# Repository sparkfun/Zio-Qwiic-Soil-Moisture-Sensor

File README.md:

SparkFun Qwiic Soil Moisture Sensor
========================================

[*SparkFun Qwiic Soil Moisture Sensor (17731)*](https://www.sparkfun.com/products/17731)

The SparkFun Qwiic Soil Moisture Sensor is a simple breakout for measuring the moisture in soil and similar materials. The soil moisture sensor is pretty straightforward to use. The two large, exposed pads function as probes for the sensor, together acting as a variable resistor. The more water that is in the soil means the better the conductivity between the pads will be, resulting in a lower resistance and a higher SIG out. This version of the Soil Moisture Sensor includes a Qwiic connector, making it even easier to use this sensor!

To get the SparkFun Soil Moisture Sensor functioning, all you will need is to connect the VCC and GND pins to your Arduino-based device (or compatible development board). You will receive a SIG out, which will depend on the amount of water in the soil. One commonly known issue with soil moisture senors is their short lifespan when exposed to a moist environment. To combat this, we’ve had the PCB coated in gold finishing (ENIG, or Electroless Nickel Immersion Gold).

Built in cooperation with [Zio Smart Prototyping](https://www.smart-prototyping.com/Zio/Zio-Qwiic-Soil-Moisture-Sensor)! 

#### Specification

* I2C address: 0x07- 0x78 (Default: 0x28)
* Gateway MCU: ATtiny85-20SU
* Probes Surface Finish: Gold Immersion
* Weight: 6.0g
* Module dimension: 20.3x 100.0mm

Documentation
--------------
* **[Hookup Guide](https://learn.sparkfun.com/tutorials/soil-moisture-sensor-hookup-guide)** - Basic hookup guide for the SparkFun Qwiic Soil Moisture Sensor.
* [ATtiny85 Gateway Firmware](https://github.com/ZIOCC/Zio-Qwiic-Soil-Moisture-Sensor/tree/master/Firmware/Qwiic_Soil_Moisture_Sensor_Gateway_Firmware/Qwiic_Soil_Moisture_Firmware)

License Information
-------------------

This product is _**open source**_! 

Please review the LICENSE.md file for license information. 

If you have any questions or concerns on licensing, please contact technical support on our [SparkFun forums](https://forum.sparkfun.com/viewforum.php?f=152).

Distributed as-is; no warranty is given.

- Your friends at SparkFun.

_<COLLABORATION CREDIT>_

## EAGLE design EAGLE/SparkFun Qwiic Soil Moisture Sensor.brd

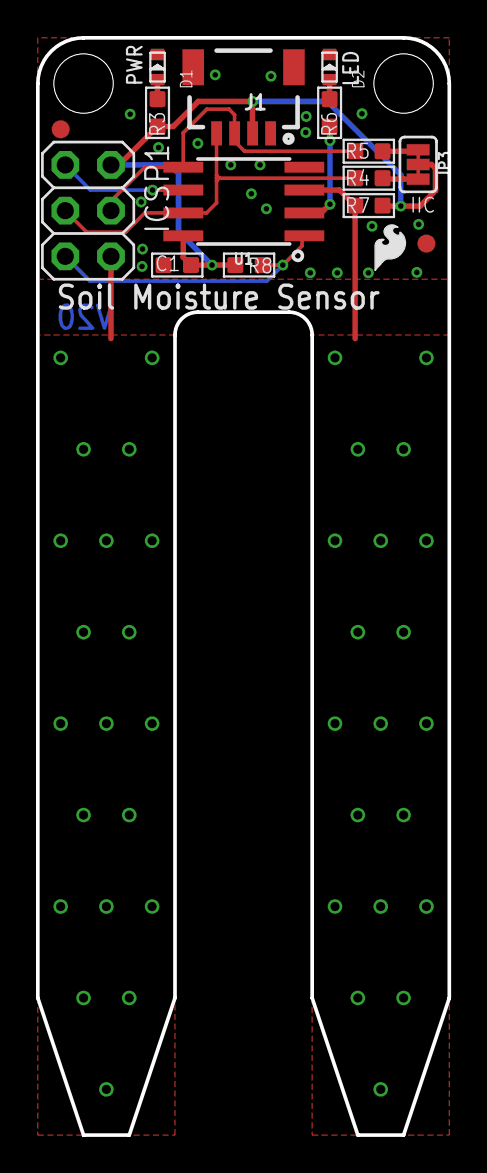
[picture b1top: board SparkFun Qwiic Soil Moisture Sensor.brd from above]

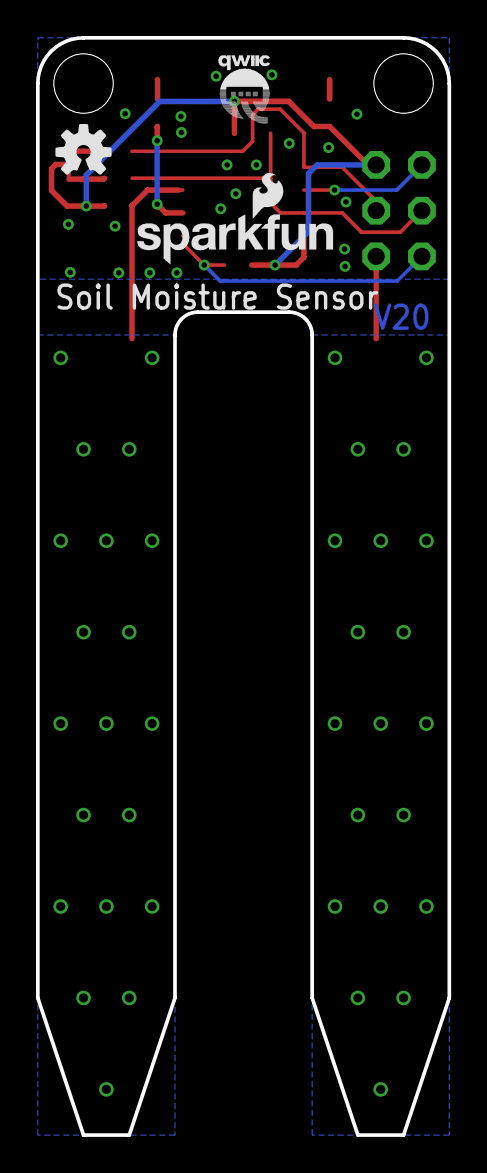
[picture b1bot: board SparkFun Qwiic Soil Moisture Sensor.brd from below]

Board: 2 copper layers, 22.9 x 61.0 mm, 21 parts (3 on the bottom side), 12 nets.

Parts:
C1: 100nF ±10% 50V; C0603
D1: RED; LED-0603
D2: GREEN; LED-0603
FID1, FID2: FIDUCIAL1X2; FIDUCIAL-1X2
ICSP1: 3x2 M; 2X03
J1: JST-SH-4P-1.0; JST-SH-4P
JP3: SMT-JUMPER_3_2-NC_TRACE
LOGO1: SFE_LOGO_NAME_FLAME.1_INCH; SFE_LOGO_NAME_FLAME_.1
LOGO2: OSHW-LOGOS; OSHW-LOGO-S
R3, R6: 1.5K ±1%; R0603
R4, R5: 4.7K ±1%; R0603
R7: 100K ±1%; R0603
R8: 10K ±1%; R0603
STANDOFF1, STANDOFF2: STAND-OFF
U1: Tiny85-20-SMT; SO08-EIAJ_MCU
U$2: SFE_LOGO_FLAME_.1
U$5: QWIIC-LOGO-SMALL

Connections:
+3V3: C1.2, ICSP1.2, J1.2, JP3.2, R3.1, R7.2, R8.2, U1.8
ADC: R7.1, U1.3
GND: C1.1, D1.-, D2.-, ICSP1.6, J1.1, J1.NC1, J1.NC2, U1.4
LED: R6.1, U1.2
MISO: ICSP1.1, U1.6
unnamed: D1.+, R3.2
unnamed: D2.+, R6.2
unnamed: JP3.3, R4.2
unnamed: JP3.1, R5.2
RST: ICSP1.5, R8.1, U1.1
SCL/SCK: ICSP1.3, J1.4, R4.1, U1.7
SDA/MOSI: ICSP1.4, J1.3, R5.1, U1.5

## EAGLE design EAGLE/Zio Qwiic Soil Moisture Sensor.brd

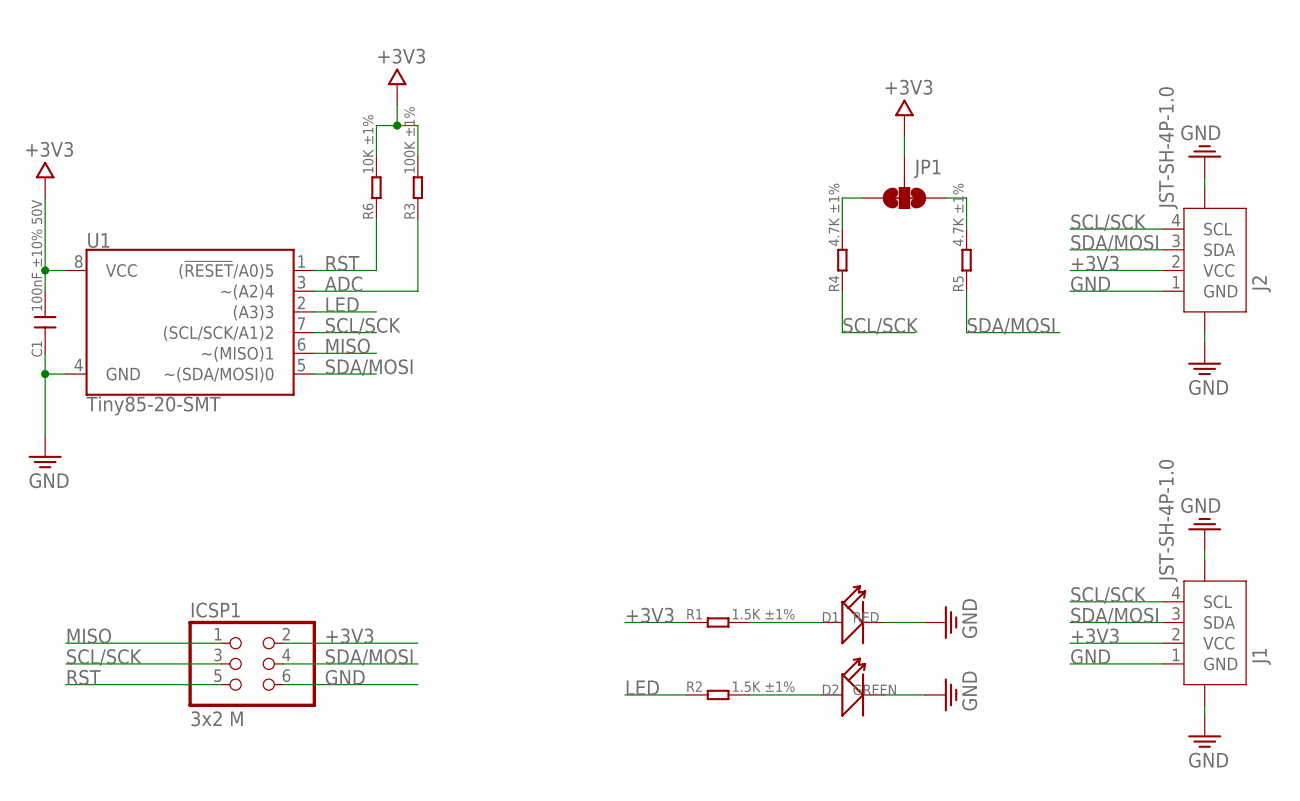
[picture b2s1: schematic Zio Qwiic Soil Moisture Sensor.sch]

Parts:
C1: 100nF ±10% 50V; C0603
D1: RED; LED-0603
D2: GREEN; LED-0603
ICSP1: 3x2 M; 2X03
J1, J2: JST-SH-4P-1.0; JST-SH-4P
JP1: SMT-JUMPER_3_2-NC_TRACE
R1, R2: 1.5K ±1%; R0603
R3: 100K ±1%; R0603
R4, R5: 4.7K ±1%; R0603
R6: 10K ±1%; R0603
U1: Tiny85-20-SMT; SO08-EIAJ_MCU

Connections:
+3V3: C1.2, ICSP1.2, J1.2 (VCC), J2.2 (VCC), JP1.2, R1.1, R3.2, R6.2, U1.8 (VCC)
ADC: R3.1, U1.3 (~(A2)4)
GND: C1.1, D1.-, D2.-, ICSP1.6, J1.1 (GND), J1.NC1 (5), J1.NC2 (6), J2.1 (GND), J2.NC1 (5), J2.NC2 (6), U1.4 (GND)
LED: R2.1, U1.2 ((A3)3)
MISO: ICSP1.1, U1.6 (~(MISO)1)
unnamed: D1.+, R1.2
unnamed: D2.+, R2.2
unnamed: JP1.3, R4.2
unnamed: JP1.1, R5.2
RST: ICSP1.5, R6.1, U1.1 ((!RESET!/A0)5)
SCL/SCK: ICSP1.3, J1.4 (SCL), J2.4 (SCL), R4.1, U1.7 ((SCL/SCK/A1)2)
SDA/MOSI: ICSP1.4, J1.3 (SDA), J2.3 (SDA), R5.1, U1.5 (~(SDA/MOSI)0)

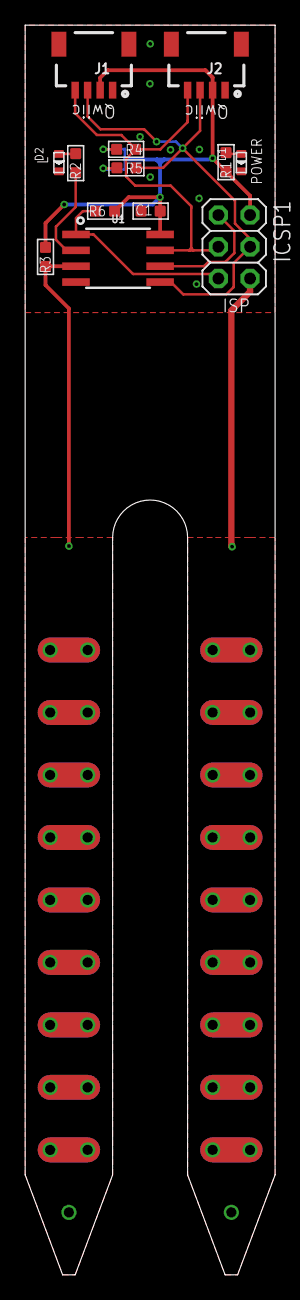
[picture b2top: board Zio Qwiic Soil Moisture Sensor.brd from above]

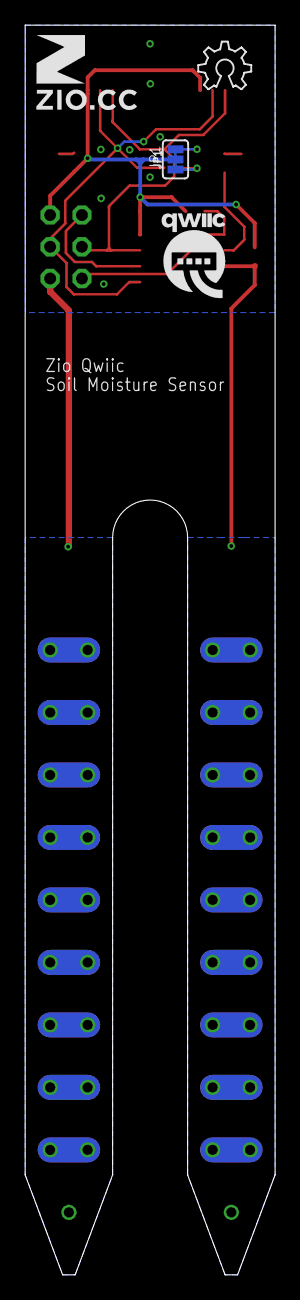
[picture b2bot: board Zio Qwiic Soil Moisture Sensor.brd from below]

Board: 2 copper layers, 20.0 x 100.0 mm, 17 parts (4 on the bottom side), 12 nets.

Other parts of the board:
U$2: 6MM
U$3: QWIIC-LOGO-MEDIUM
U$4: OSHW_6X150_NOTEXT

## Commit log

2021-01-27 Updating Board File. Schematic to come
    Updating Board File. Waiting on Schematic.
2021-01-27 Updating brd and sch to match

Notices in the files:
parts and their libraries:
SparkFun-Aesthetics: Licensing: Creative Commons ShareAlike 4.0 International - https://creativecommons.org/licenses/by-sa/4.0
